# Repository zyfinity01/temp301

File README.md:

# Open Data Recorder for Environmental Monitoring

An open source and open hardware IoT-connected SDI-12-enabled remote data recorder capable of deployment for environmental monitoring by New Zealand Regional Councils.

## Quick Links

- [Project Charter](docs/charter.md)
- [Meetings](https://gitlab.ecs.vuw.ac.nz/engr489-environment-monitoring/engr489-project/issues?scope=all&utf8=%E2%9C%93&state=all&label_name%5B%5D=Meeting)
- [Development Guide](docs/technical/README.md)

## Project Description

Regional Councils maintain large environmental monitoring networks with real-time data recorded by data recorders being reported via telemetry to virtual servers at a data centre.

This project arose from the desire of the Hydrology Team at Greater Wellington Council to explore the benefits that IoT technologies could offer &mdash; low-cost hardware, low power consumption, future-proof communication technologies and the ability of Council staff to extend the capabilities of the data recorder &mdash; whilst maintaining the sensor accuracy required for scientific studies and regulatory functions. In collaboration with staff and students at the School of Engineering and Computer Science at Victoria University of Wellington, a prototype data recorder has been developed to meet the environmental monitoring requirements of they Hydrology Team.

## Project Requirements

Overarching project requirements are listed in [docs/requirements/requirements.md](docs/requirements/requirements.md).

- Revision 3 requirements are listed in [docs/requirements/requirements_for_Rev 3.0](docs/requirements/requirements_for_Rev 3.0).
- Revision 4 requirements are the same as Revision 3.

## Overall Objectives

- Develop a system to enable more cost effective collection of data to serve the Region's environmental data needs.
- Deliver an 'Open-Source' system that is fully documented which will allow GWRC staff to up-skill and understand IoT concepts and provide GWRC IT department the ability to support the server and data transfer components in the future. Hardware construction would need to be well documented to allow future production of devices post-project.
- Enable future development of the system in collaboration with VUW.
- Develop a system that could be offered to other Regional Councils around New Zealand if successful.

The project can be as big or as small as the project team decides. The main thing is to ensure we end up with a robust, accurate system that can be evaluated against our current systems. GWRC will be able to provide test sites locations and VUW project team will be able exposed to the work the council undertakes - Field trip(s)?

GWRC doesn't have any set funding for the project and monetary contributions can be discussed if the project is of interest to VUW. I should imagine GWRC would be able to pay for the virtual server chargers, software licences and hardware but that is to be confirmed with management.

## Repository Directory Structure

### High level overview

```text
Environmental-Monitoring-2020/engr489-project/
├── docs
├── software
    ├── device
        ├── embedded
        └── webapp
    ├── server
    └── simulator
├── hardware
├── util
└── venv
```

### `software`: Embedded Software and Device Simulators

#### `device`: Embedded Software, Web-App Code

```text
device
├── build
├── embedded
└── webapp
```

- `build`: automatically created by the software build script, `build.sh`.
- `embedded`: Micropython device code &mdash; development takes place here.
- `webapp`: preact web app code &mdash; development takes place here.

#### `server`: scripts for communication with remote servers

```text
server/
[no subdirectories]
```

Python scripts for publishing to an MQTT broker and subscribing to topics. Also contains a Python script for publishing to Microsoft Power BI <https://powerbi.microsoft.com/>. Used during exploration of different protocols for transmitting data from the data recorder.

#### `simulator`: Simulation Scripts

```text
simulator/
[no subdirectories]
```

Various scripts for simulating different parts of the project.

### `docs`: Documents and Documentation

```text
docs
├── bom
├── datasheets
├── development
├── literature
├── meetings
├── presentations
├── reports
├── requirements
├── research
└── technical
```

- `bom`: Bill of Materials (BoM) documents sent for PCB manufacture.
- `technical`: technical documentation, including documentation of the tinyweb server implementation which runs on the ESP32 to provide a web interface to the data recorder.
- `literature`: A flat folder containing PDF copies of anything that will or could be cited in the reports: journal articles, tech notes, etc.  There should be a BibTeX .bib bibliography file at the same level as the PDF files, for use with the JabRef open source bibliography and reference manager.
- `meetings`: saved emails from the 2021 Honours project.
- `presentations`: The files used in any presentations, including the ENGR 489 course final presentation.
- `reports`: Contains the ENGR 489 course reports. There are two reports required this year, a Preliminary Report and a Final Report. LaTeX source files. R, Matlab, etc. files, containing only the figures used in the report at this level. One sub-folder "Figures" to keep figures organised.
- `requirements`: documentation provided by the clients for project requirements.
- `research`: Embedded software, Web App, Hardware Design and PCB development notes.

### `hardware`: Data Recorder Hardware

```text
hardware/
├── reviews
└── schematics
```

- `reviews`: documentation of schematics and PCB reviews.
- `schematics`: electronic schematics and PCB designs of the current revision.

### `util`: utility scripts

```text
util/
├── Docker
├── ansible
├── micropython-hitl
├── micropython-software
├── scripts
└── vagrant
```

Build and test scripts, including development and test environment provisioning and configuration scripts, for performing utility functions separate from the software running on the data recorder.

- `Docker`: Dockerfiles to create images used in jobs in the GitLab CI pipeline.
- `ansible`: Ansible playbooks for provisioning development, build and test environments.
- `micropython-hitl`: hardware-in-the-loop (HTL) testing scripts.
- `micropython-software`: Dockerfile for running MicroPython in a Docker container for development and test purposes.
- `scripts`: build and test scripts mostly intended to be run in the CI pipeline.
- `vagrant`: Vagrantfile for testing of provisioning and configuration of HTL build and test servers in a VirtualBox VM.

### `venv`: Python Virtual Environment

Python virtual environment created when the instructions in the _Development Environment_ section of the [Technical Documentation](docs/technical/README.md) are followed.

---

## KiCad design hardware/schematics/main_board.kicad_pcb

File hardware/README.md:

# Hardware

Information about the design of the hardware and evaluation can be found in this repository.

We are using KiCad 6.0. For migrate Altium project to KiCad. KiCad 6.0 is not backward-compatible, please update you KiCad to 6.0 to view the schematics and PCB layout.

- [Schematics](schematics/)
- [Reviews](reviews/)
- [Evaluation](power_consumption_Rev3)

---

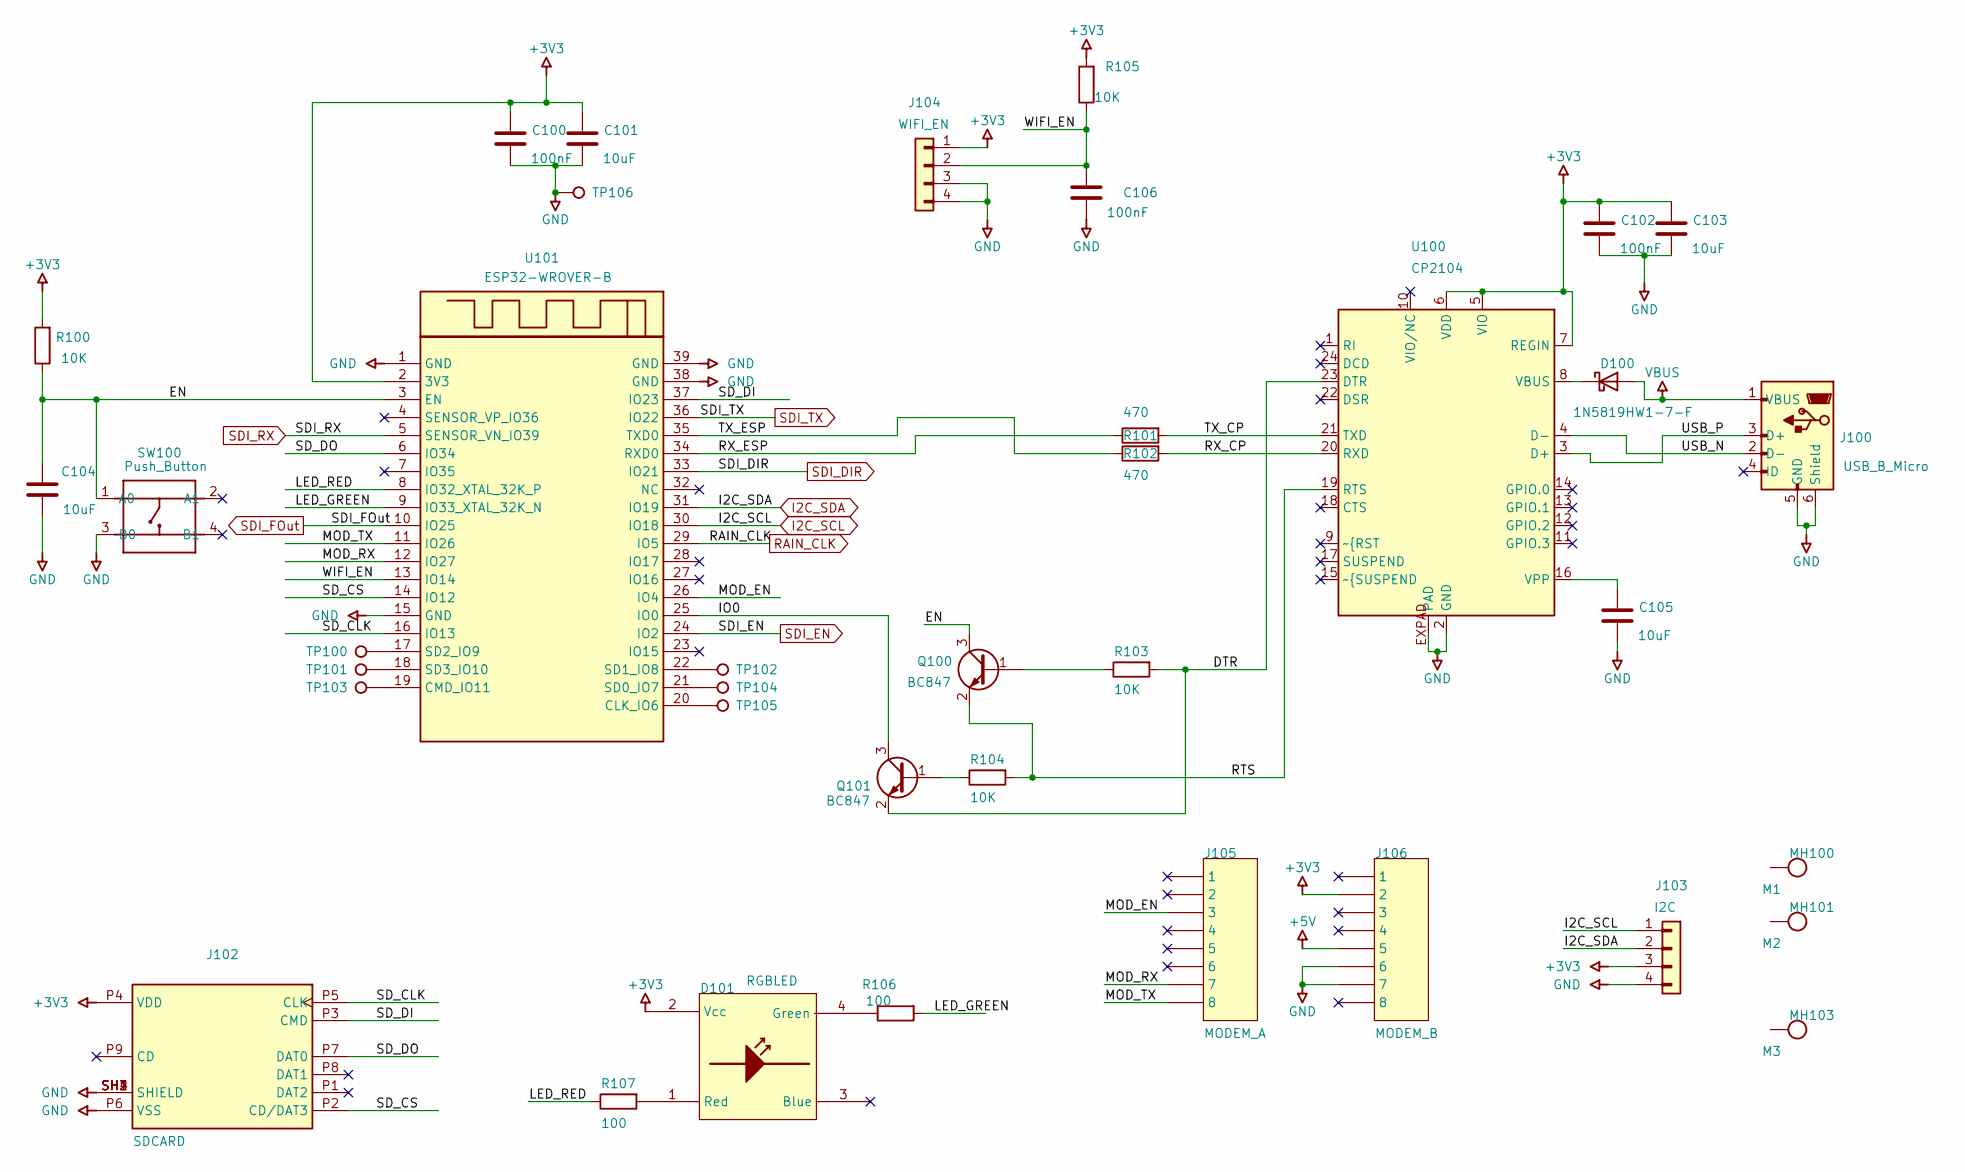
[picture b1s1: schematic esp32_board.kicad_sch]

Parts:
C100, C102, C106: 100nF; CAPC1608X80N
C101, C103, C104, C105: 10uF; CAPC2012X90N
D100: 1N5819HW1-7-F; SODFL3700X115N
D101: RGBLED; LED_APTF1616SEEZGQBDC_SM; MANUFACTURER PART NO APTF1616SEEZGQBDC
J100: USB_B_Micro; CON_1050170001
J102: SDCARD; CON_MEM2075-00-140-01-A; PARTREV A
J103: I2C; CON_NPTC041KFXC-RC_SM
J104: WIFI_EN; CON_NPTC041KFXC-RC_SM
J105: MODEM_A; CON_0878980826_SM
J106: MODEM_B; CON_0878980826_SM
MH100: M1; HOLN_M3
MH101: M2; HOLN_M3
MH103: M3; HOLN_M3
Q100, Q101: BC847; SOT95P240X130_123-3N
R100, R103, R104, R105: 10K; RESC1608X50N
R101, R102: 470; RESC1608X50N
R106, R107: 100; RESC1608X50N
SW100: Push_Button; SW_B3S-1000P_SM; MPN DTSM-62K-S-V-T/R(SN431)
TP100, TP101, TP102, TP103, TP104, TP105, TP106: RevPol; TP150
U100: CP2104; QFN50P400X400X90-25N
U101: ESP32-WROVER-B; IC_ESP32-WROVER

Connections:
+3V3: C100.1, C101.1, C102.1, C103.1, D101.2 (Vcc), J102.P4 (VDD), J103.3, J104.1, J106.2, R100.2, R105.1, U100.5 (VIO), U100.6 (VDD), U100.7 (REGIN), U101.2 (3V3); also elsewhere on the board
+5V: J106.5; also elsewhere on the board
/esp32_board/DTR: Q101.2 (E), R103.1, U100.23 (DTR)
/esp32_board/EN: C104.1, Q100.3 (C), R100.1, SW100.1 (A0), U101.3 (EN)
/esp32_board/IO0: Q101.3 (C), U101.25 (IO0)
/esp32_board/LED_GREEN: R106.1, U101.9 (IO33_XTAL_32K_N)
/esp32_board/LED_RED: R107.2, U101.8 (IO32_XTAL_32K_P)
/esp32_board/MOD_EN: J105.3, U101.26 (IO4)
/esp32_board/MOD_RX: J105.7, U101.12 (IO27)
/esp32_board/MOD_TX: J105.8, U101.11 (IO26)
/esp32_board/RTS: Q100.2 (E), R104.1, U100.19 (RTS)
/esp32_board/RX_CP: R102.1, U100.20 (RXD)
/esp32_board/RX_ESP: R101.2, U101.34 (RXD0)
/esp32_board/SD_CLK: J102.P5 (CLK), U101.16 (IO13)
/esp32_board/SD_CS: J102.P2 (CD/DAT3), U101.14 (IO12)
/esp32_board/SD_DI: J102.P3 (CMD), U101.37 (IO23)
/esp32_board/SD_DO: J102.P7 (DAT0), U101.6 (IO34)
/esp32_board/TX_CP: R101.1, U100.21 (TXD)
/esp32_board/TX_ESP: R102.2, U101.35 (TXD0)
/esp32_board/USB_N: J100.2 (D-), U100.4 (D-)
/esp32_board/USB_P: J100.3 (D+), U100.3 (D+)
/esp32_board/WIFI_EN: C106.1, J104.2, R105.2, U101.13 (IO14)
GND: C100.2, C101.2, C102.2, C103.2, C104.2, C105.2, C106.2, J100.5 (GND), J100.6 (Shield), J102.P6 (VSS), J102.SH1 (SHIELD), J102.SH2 (SHIELD), J102.SH3 (SHIELD), J102.SH4 (SHIELD), J103.4, J104.3, J104.4, J106.6, J106.7, SW100.3 (B0), TP106.1, U100.2 (GND), U100.EXPAD (PAD), U101.1 (GND), U101.15 (GND), U101.38 (GND), U101.39 (GND); also elsewhere on the board
I2C_SCL: J103.1, U101.30 (IO18); also elsewhere on the board
I2C_SDA: J103.2, U101.31 (IO19); also elsewhere on the board
unnamed: C105.1, U100.16 (VPP)
unnamed: D100.K, U100.8 (VBUS)
unnamed: D101.1 (Red), R107.1
unnamed: D101.4 (Green), R106.2
unnamed: Q100.1 (B), R103.2
unnamed: Q101.1 (B), R104.2
unnamed: TP100.1, U101.17 (SD2_IO9)
unnamed: TP101.1, U101.18 (SD3_IO10)
unnamed: TP102.1, U101.22 (SD1_IO8)
unnamed: TP103.1, U101.19 (CMD_IO11)
unnamed: TP104.1, U101.21 (SD0_IO7)
unnamed: TP105.1, U101.20 (CLK_IO6)
RAIN_CLK: U101.29 (IO5); also elsewhere on the board
SDI_DIR: U101.33 (IO21); also elsewhere on the board
SDI_EN: U101.24 (IO2); also elsewhere on the board
SDI_FOut: U101.10 (IO25); also elsewhere on the board
SDI_RX: U101.5 (SENSOR_VN_IO39); also elsewhere on the board
SDI_TX: U101.36 (IO22); also elsewhere on the board
VBUS: D100.A, J100.1 (VBUS); also elsewhere on the board

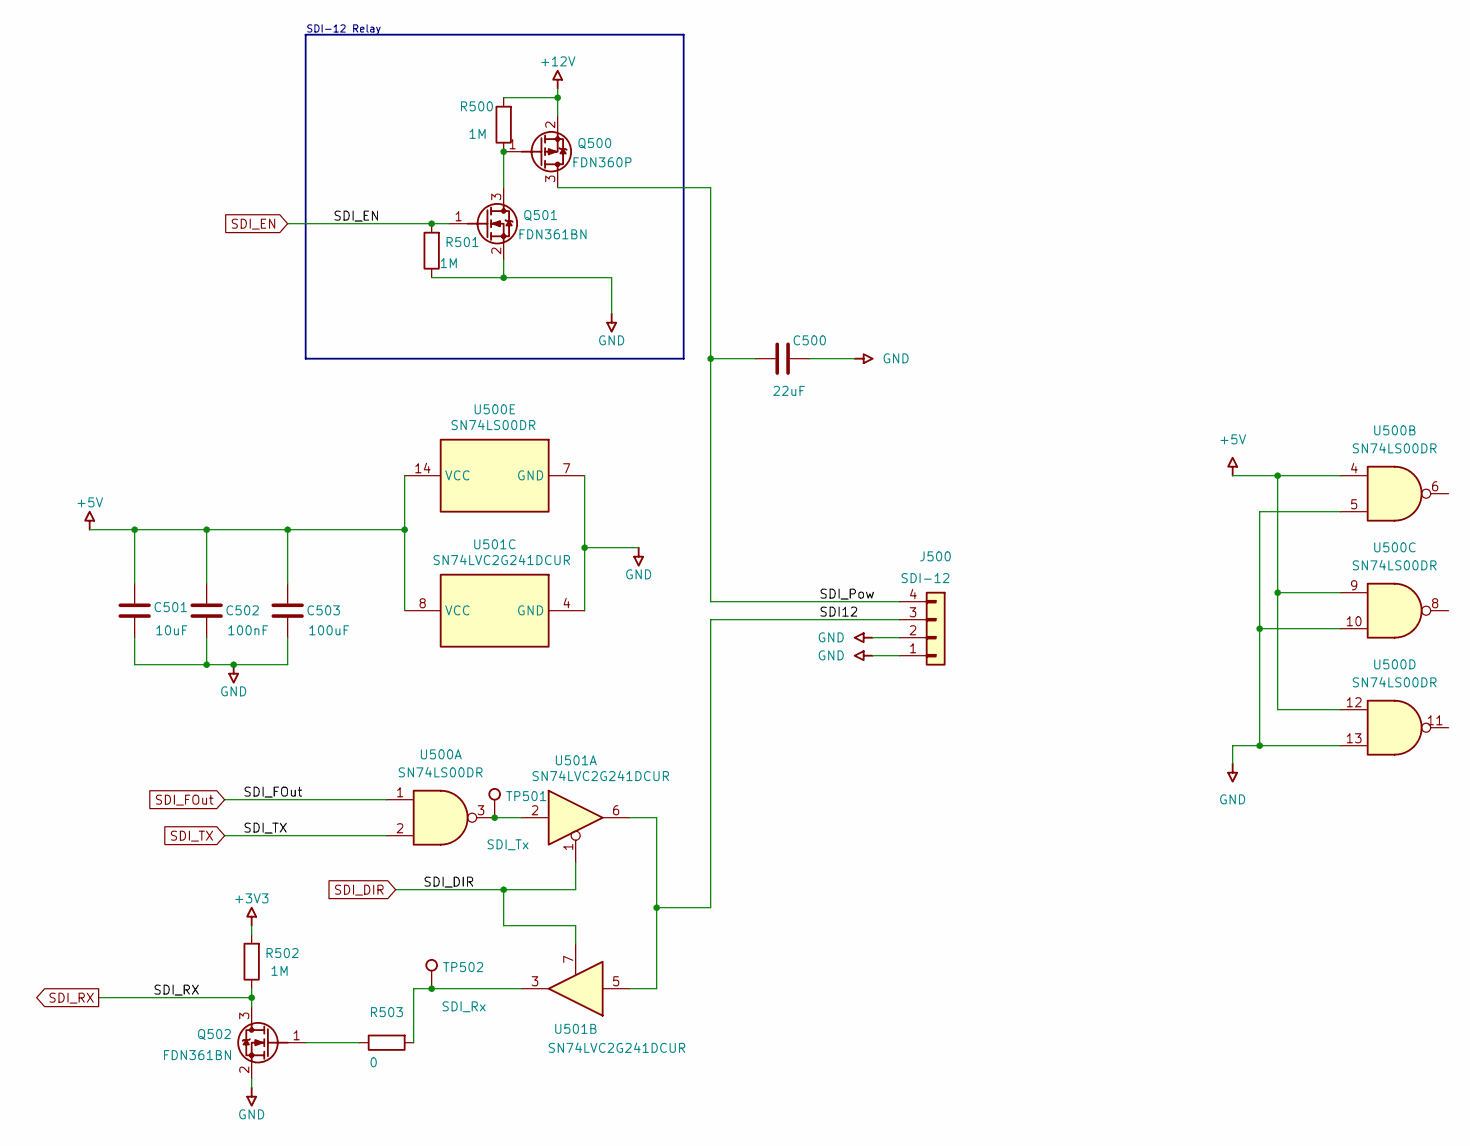
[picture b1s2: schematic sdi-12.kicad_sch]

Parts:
C500: 22uF; CAPC2012X90N
C501: 10uF; CAPC2012X90N
C502: 100nF; CAPC1608X80N
C503: 100uF; CAPC1608X80N
J500: SDI-12; CON_691508110304_SM
Q500: FDN360P; SOT95P240X110_123_SUPER-3N
Q501, Q502: FDN361BN; SOT95P240X110_231_SUPER-3N
R500, R501, R502: 1M; RESC1608X50N
R503: 0; RESC1608X50N
TP501: SDI_Tx; TP150
TP502: SDI_Rx; TP150
U500: SN74LS00DR; SOIC127P600X175-14N
U501: SN74LVC2G241DCUR; SOP50P320X90-8N

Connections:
+3V3: R502.1; also elsewhere on the board
+5V: C501.1, C502.1, C503.1, U500.4, U500.9, U500.12, U500.14 (VCC), U501.8 (VCC); also elsewhere on the board
+12V: Q500.2 (S), R500.1; also elsewhere on the board
/sdi-12/SDI12: J500.3, U501.5, U501.6
/sdi-12/SDI_Pow: C500.2, J500.4, Q500.3 (D)
GND: C500.1, C501.2, C502.2, C503.2, J500.1, J500.2, Q501.2 (S), Q502.2 (S), R501.2, U500.5, U500.7 (GND), U500.10, U500.13, U501.4 (GND); also elsewhere on the board
unnamed: Q500.1 (G), Q501.3 (D), R500.2
unnamed: Q502.1 (G), R503.2
unnamed: R503.1, TP502.1, U501.3
unnamed: TP501.1, U500.3, U501.2
SDI_DIR: U501.1, U501.7; also elsewhere on the board
SDI_EN: Q501.1 (G), R501.1; also elsewhere on the board
SDI_FOut: U500.1; also elsewhere on the board
SDI_RX: Q502.3 (D), R502.2; also elsewhere on the board
SDI_TX: U500.2; also elsewhere on the board

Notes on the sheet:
SDI-12 Relay

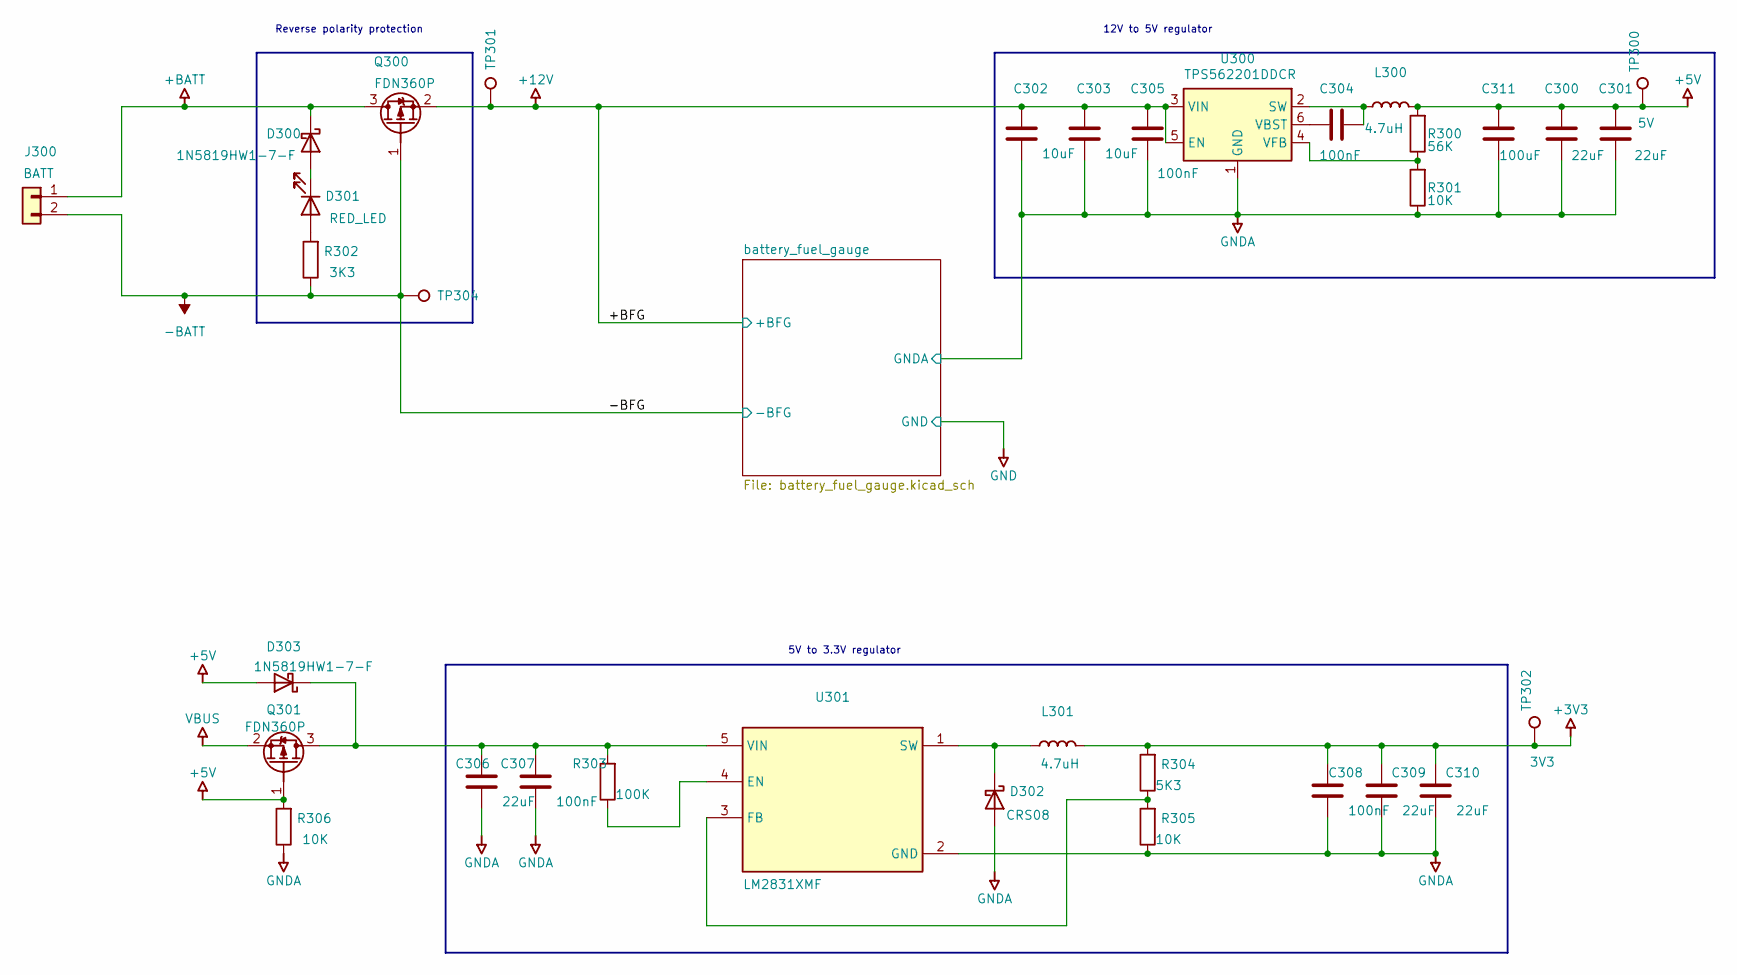
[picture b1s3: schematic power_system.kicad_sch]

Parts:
C300, C301, C306, C309, C310: 22uF; CAPC2012X90N
C302, C303: 10uF; CAPC2012X90N
C304, C305, C307, C308: 100nF; CAPC1608X80N
C311: 100uF; CAPC1608X80N
D300, D303: 1N5819HW1-7-F; SODFL3700X115N
D301: RED_LED; LED_19-217/B7C-ZL2N1B3X/3T_SM
D302: CRS08; SODFL3500X98N
J300: BATT; WURTH_691709710302
L300, L301: 4.7uH; IND_SRN5040-4R7M_SM
Q300, Q301: FDN360P; SOT95P240X110_123_SUPER-3N
R300: 56K; RESC1608X50N
R301, R305, R306: 10K; RESC1608X50N
R302: 3K3; RESC2012X50N
R303: 100K; RESC1608X50N
R304: 5K3; RESC1608X50N
TP300: 5V; TP150
TP301, TP304: RevPol; TP150
TP302: 3V3; TP150
U300: TPS562201DDCR; SOT95P305X110-6N
U301: LM2831XMF; SOT95P279X142-12345-5N

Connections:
+3V3: C308.1, C309.1, C310.1, L301.2, R304.1, TP302.1; also elsewhere on the board
+5V: C300.1, C301.1, C311.1, D303.A, L300.2, Q301.1 (G), R300.1, R306.2, TP300.1; also elsewhere on the board
+12V: C302.1, C303.1, C305.1, Q300.2 (S), TP301.1, U300.3 (VIN), U300.5 (EN); also elsewhere on the board
+BATT: D300.K, J300.1, Q300.3 (D)
-BATT: J300.2, Q300.1 (G), R302.2, TP304.1; also elsewhere on the board
GNDA: C300.2, C301.2, C302.2, C303.2, C305.2, C306.2, C307.2, C308.2, C309.2, C310.2, C311.2, D302.A, R301.2, R305.2, R306.1, U300.1 (GND), U301.2 (GND); also elsewhere on the board
unnamed: C304.1, L300.1, U300.2 (SW)
unnamed: C304.2, U300.6 (VBST)
unnamed: C306.1, C307.1, D303.K, Q301.3 (D), R303.1, U301.5 (VIN)
unnamed: D300.A, D301.K
unnamed: D301.A, R302.1
unnamed: D302.K, L301.1, U301.1 (SW)
unnamed: R300.2, R301.1, U300.4 (VFB)
unnamed: R303.2, U301.4 (EN)
unnamed: R304.2, R305.1, U301.3 (FB)
VBUS: Q301.2 (S); also elsewhere on the board

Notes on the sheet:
12V to 5V regulator
Reverse polarity protection
5V to 3.3V regulator

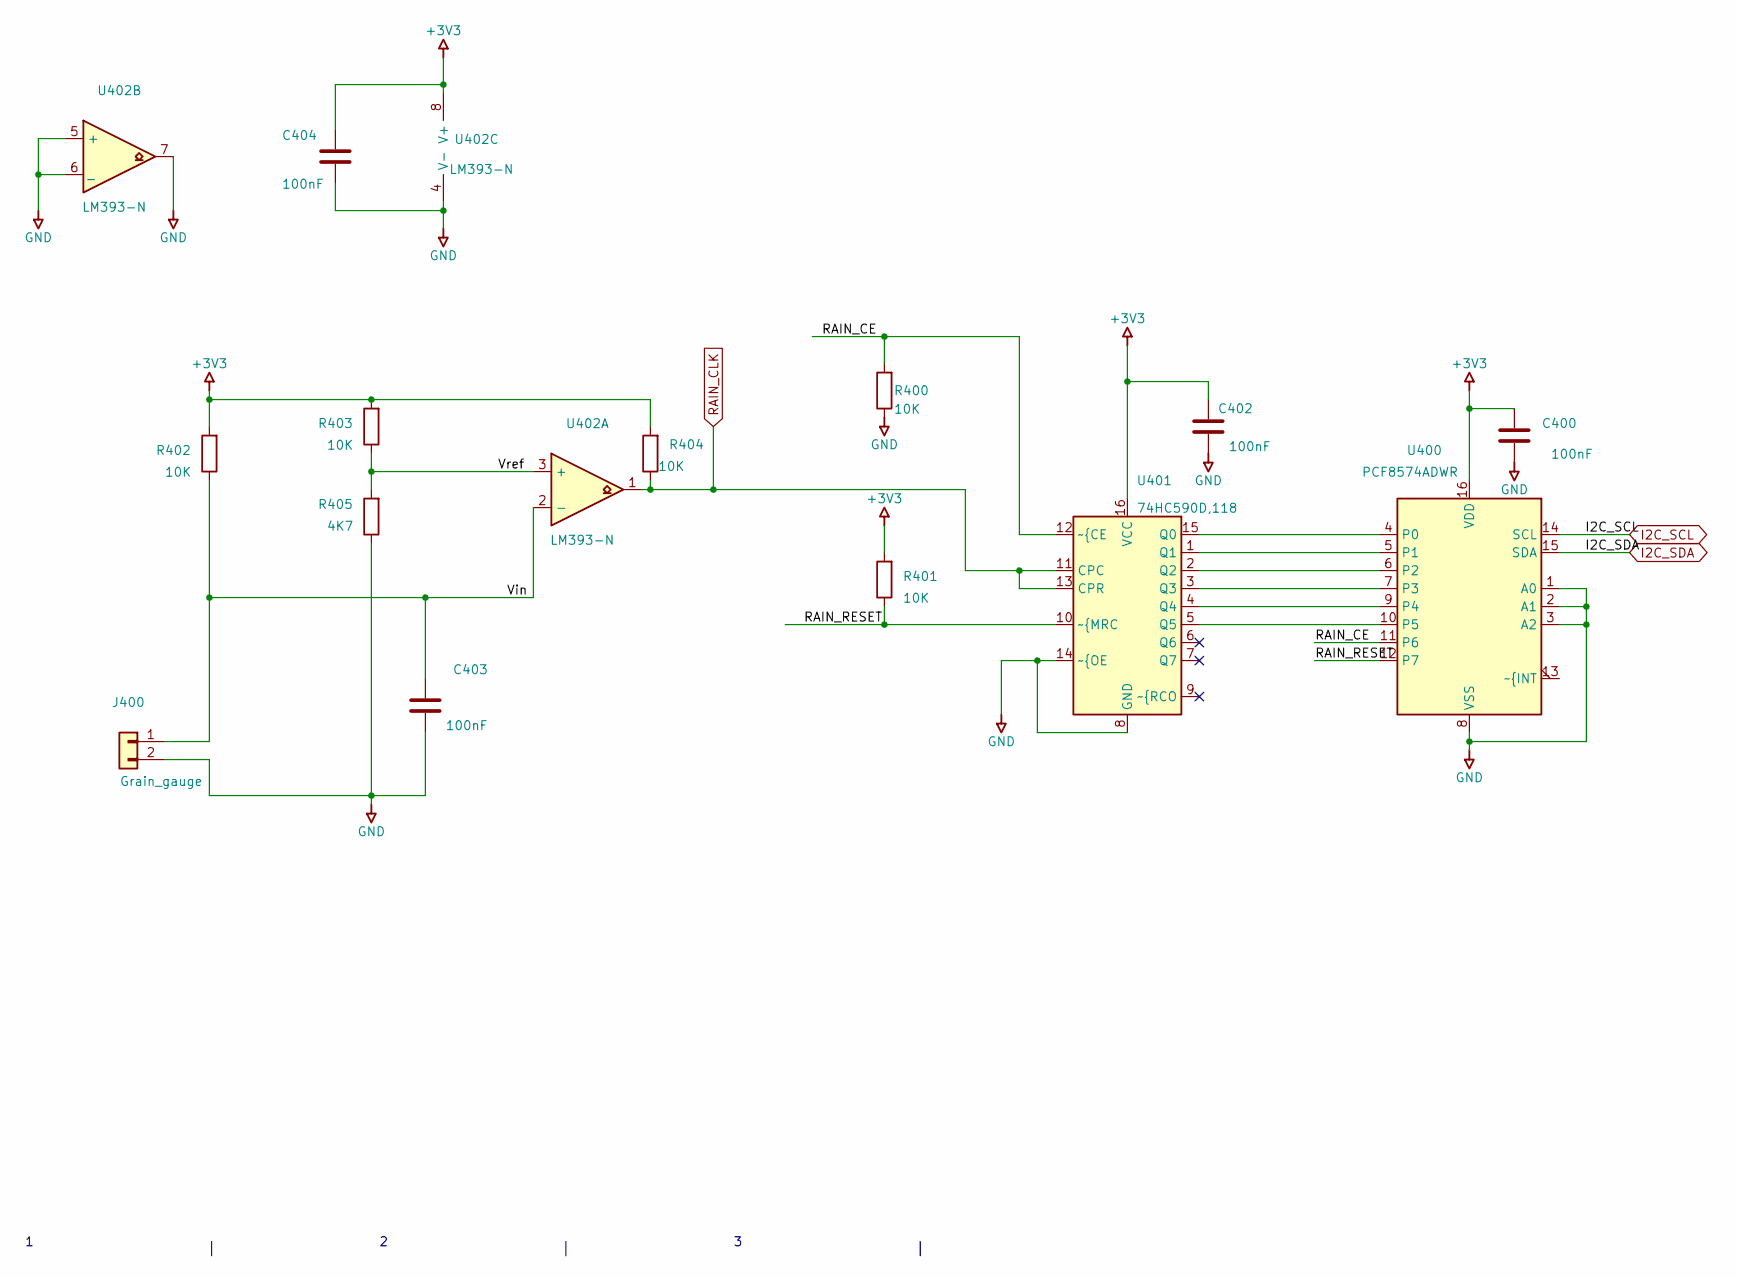
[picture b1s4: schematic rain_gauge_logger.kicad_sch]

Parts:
C400, C402, C403, C404: 100nF; CAPC1608X80N
J400: Grain_gauge; WURTH_691709710302
R400, R401, R402, R403, R404: 10K; RESC1608X50N
R405: 4K7; RESC1608X50N
U400: PCF8574ADWR; SOIC127P1030X265-16N
U401: 74HC590D,118; SOIC127P600X175-16N
U402: LM393-N; SOIC127P600X175-8N

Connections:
+3V3: C400.1, C402.2, C404.2, R401.1, R402.1, R403.1, R404.1, U400.16 (VDD), U401.16 (VCC), U402.8 (V+); also elsewhere on the board
/rain_gauge_logger/RAIN_CE: R400.1, U400.11 (P6), U401.12 (~{CE)
/rain_gauge_logger/RAIN_RESET: R401.2, U400.12 (P7), U401.10 (~{MRC)
/rain_gauge_logger/Vin: C403.2, J400.1, R402.2, U402.2 (-)
/rain_gauge_logger/Vref: R403.2, R405.1, U402.3 (+)
GND: C400.2, C402.1, C403.1, C404.1, J400.2, R400.2, R405.2, U400.1 (A0), U400.2 (A1), U400.3 (A2), U400.8 (VSS), U401.8 (GND), U401.14 (~{OE), U402.4 (V-), U402.5 (+), U402.6 (_), U402.7; also elsewhere on the board
I2C_SCL: U400.14 (SCL); also elsewhere on the board
I2C_SDA: U400.15 (SDA); also elsewhere on the board
unnamed: U400.4 (P0), U401.15 (Q0)
unnamed: U400.5 (P1), U401.1 (Q1)
unnamed: U400.6 (P2), U401.2 (Q2)
unnamed: U400.7 (P3), U401.3 (Q3)
unnamed: U400.9 (P4), U401.4 (Q4)
unnamed: U400.10 (P5), U401.5 (Q5)
RAIN_CLK: R404.2, U401.11 (CPC), U401.13 (CPR), U402.1; also elsewhere on the board

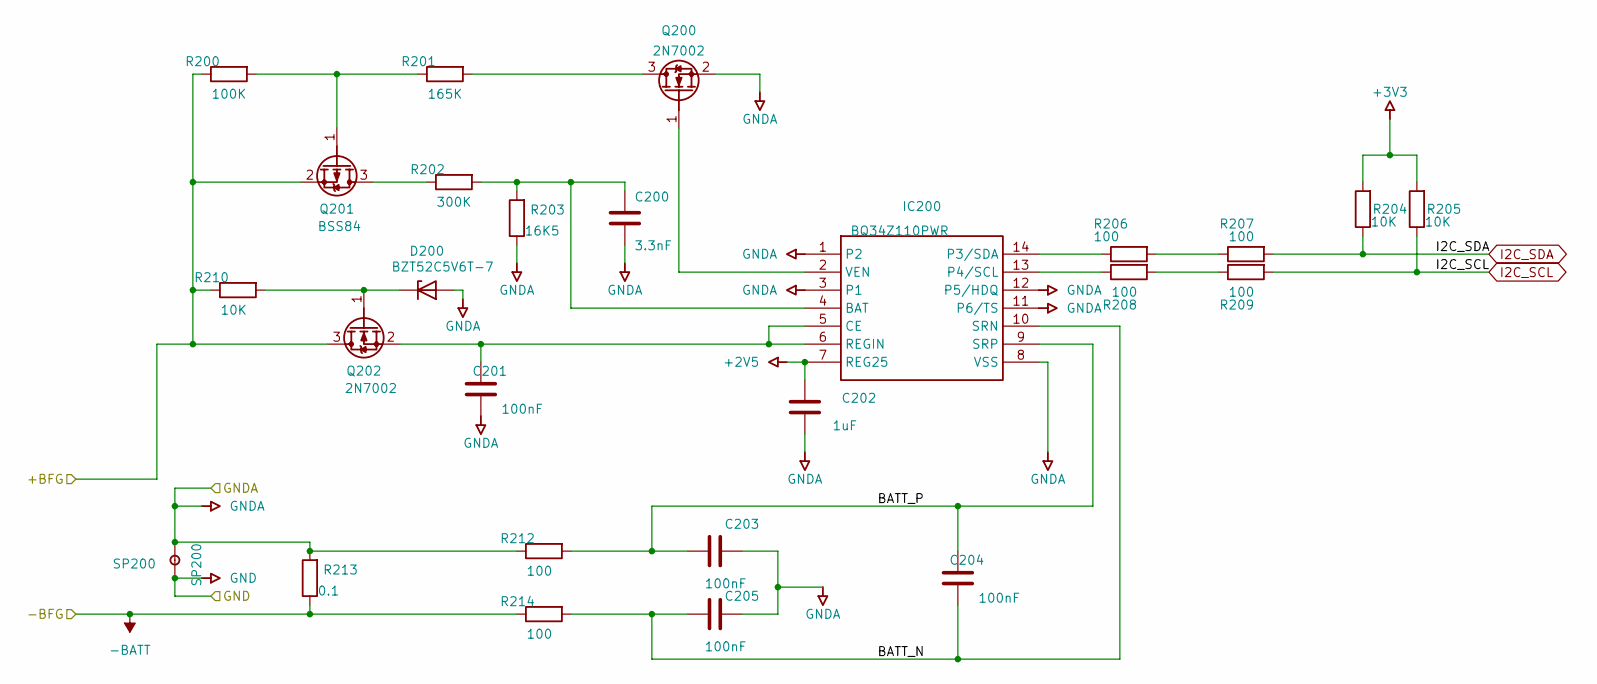
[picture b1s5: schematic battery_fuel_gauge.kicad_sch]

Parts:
C200: 3.3nF; CAPC1608X80N
C201, C203, C204, C205: 100nF; CAPC1608X80N
C202: 1uF; CAPC1608X80N
D200: BZT52C5V6T-7; SOD523
IC200: BQ34Z110PWR; SOP65P640X120-14N; MANUFACTURER_PART_NUMBER BQ34Z110PWR; MOUSER PART NUMBER 595-BQ34Z110PWR
Q200, Q202: 2N7002; SOT95P240X130_123-3N
Q201: BSS84; SOT95P240X130_123-3N
R200: 100K; RESC1608X50N
R201: 165K; RESC1608X50N
R202: 300K; RESC1608X50N
R203: 16K5; RESC1608X50N
R204, R205, R210: 10K; RESC1608X50N
R206, R207, R208, R209, R212, R214: 100; RESC1608X50N
R213: 0.1; RESC2012X50N
SP200: SP200; STAR_TH_2P

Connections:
+2V5: C202.2, IC200.7 (REG25)
+3V3: R204.1, R205.1; also elsewhere on the board
+12V: Q201.2 (S), Q202.3 (D), R200.1, R210.1; also elsewhere on the board
-BATT: R213.2, R214.1; also elsewhere on the board
/power_system/battery_fuel_gauge/BATT_N: C204.1, C205.2, IC200.10 (SRN), R214.2
/power_system/battery_fuel_gauge/BATT_P: C203.2, C204.2, IC200.9 (SRP), R212.2
GND: SP200.1; also elsewhere on the board
GNDA: C200.2, C201.1, C202.1, C203.1, C205.1, D200.A, IC200.1 (P2), IC200.3 (P1), IC200.8 (VSS), IC200.11 (P6/TS), IC200.12 (P5/HDQ), Q200.2 (S), R203.2, R212.1, R213.1, SP200.2; also elsewhere on the board
I2C_SCL: R205.2, R209.2; also elsewhere on the board
I2C_SDA: R204.2, R207.2; also elsewhere on the board
unnamed: C200.1, IC200.4 (BAT), R202.2, R203.1
unnamed: C201.2, IC200.5 (CE), IC200.6 (REGIN), Q202.2 (S)
unnamed: D200.K, Q202.1 (G), R210.2
unnamed: IC200.2 (VEN), Q200.1 (G)
unnamed: IC200.13 (P4/SCL), R208.1
unnamed: IC200.14 (P3/SDA), R206.1
unnamed: Q200.3 (D), R201.2
unnamed: Q201.1 (G), R200.2, R201.1
unnamed: Q201.3 (D), R202.1
unnamed: R206.2, R207.1
unnamed: R208.2, R209.1
